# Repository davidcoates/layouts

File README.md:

# keyboards

Everything related to my keyboards.

## Keymaps

QMK "external userspace" layout: keymap sources live under
`keyboards/<keyboard>/keymaps/davidcoates`. Requires Docker.

```
./build nyquist   # compile only, output in bin/
./flash nyquist   # compile (if needed) and flash
```

shannon is defined in this repo (rather than in qmk_firmware) and needs one
firmware per hand -- see `keyboards/shannon/readme.md`:

```
./build shannon-left
./flash shannon-right
```

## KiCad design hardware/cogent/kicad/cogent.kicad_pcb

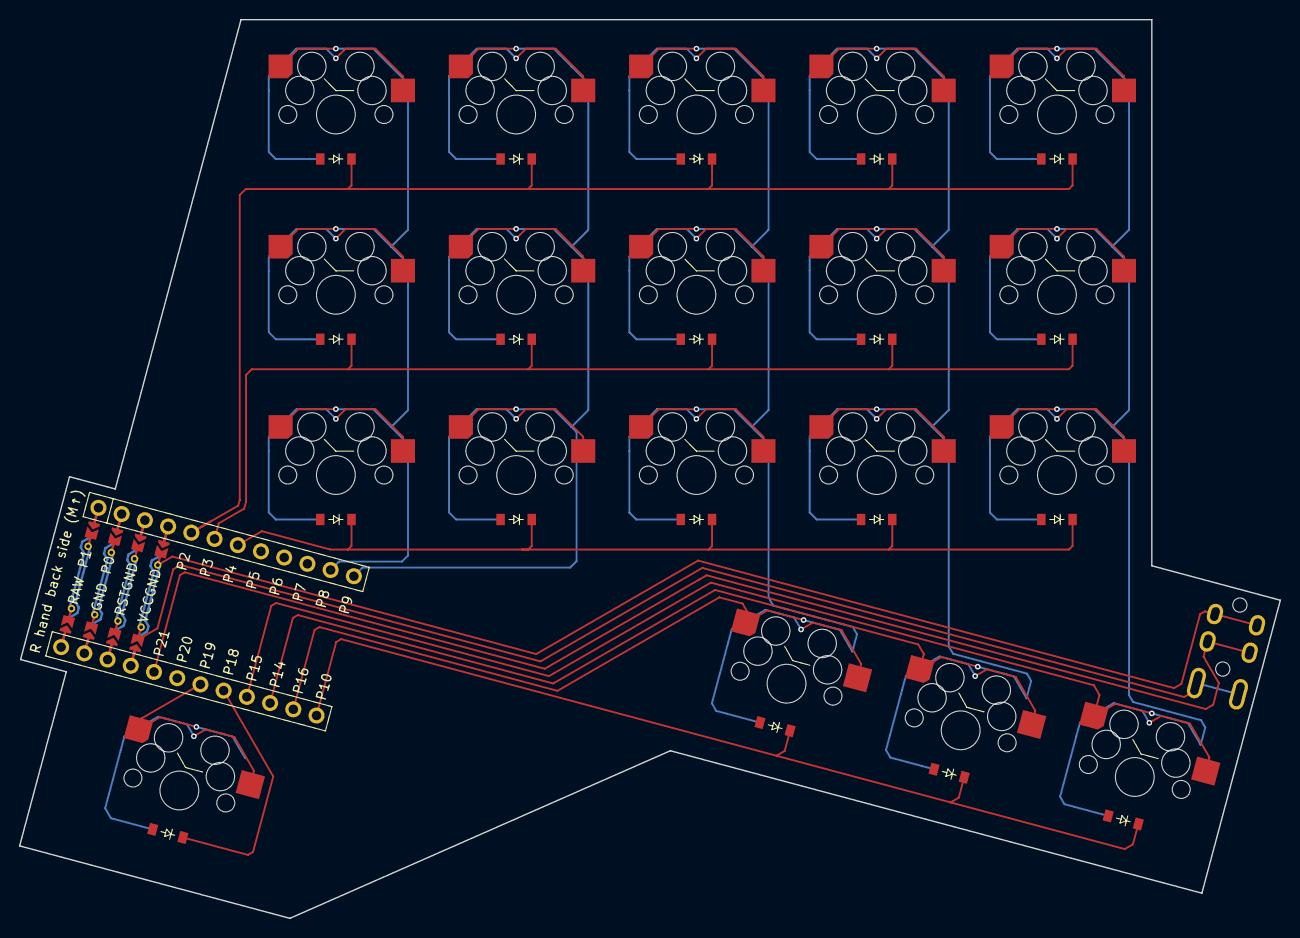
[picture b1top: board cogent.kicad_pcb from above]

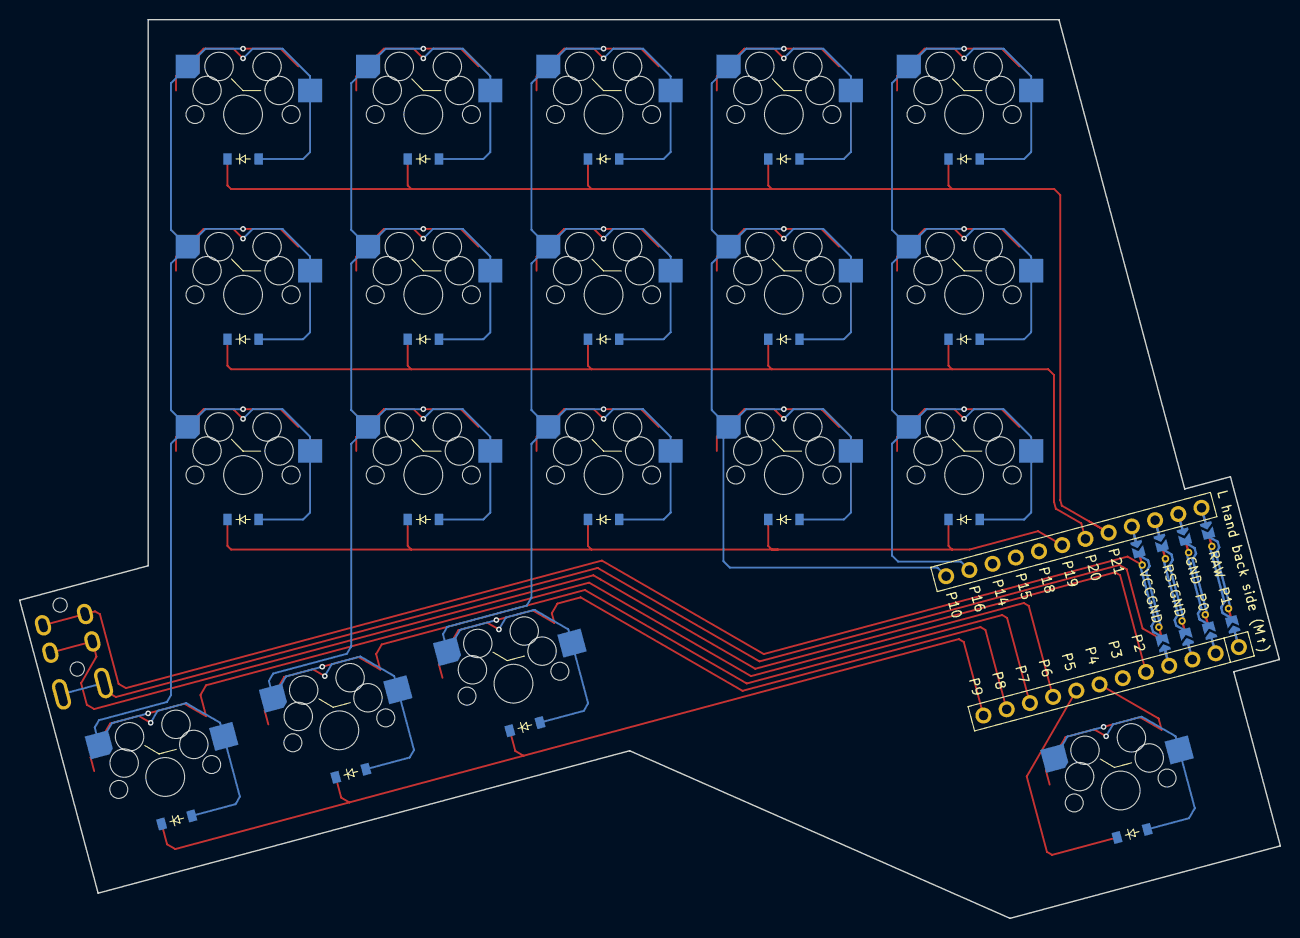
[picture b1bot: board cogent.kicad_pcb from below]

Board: 2 copper layers, 133.2 x 95.0 mm, 40 parts (19 on the bottom side), 33 nets.

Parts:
D1, D2, D3, D4, D5, D6, D7, D8, D9, D10, D11, D12, D13, D14, D15, D16, D17, D18, D19: diode_tht_sod123
MCU1: mcu_nice_nano
S1, S2, S3, S4, S5, S6, S7, S8, S9, S10, S11, S12, S13, S14, S15, S16, S17, S18, S19: switch_mx
TRRS1: trrs_pj320a (reversible, symmetric)

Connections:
GND: MCU1.103, MCU1.104, MCU1.123, TRRS1.2
P2: D3.1, D6.1, D9.1, D12.1, D15.1, MCU1.5
P3: D2.1, D5.1, D8.1, D11.1, D14.1, MCU1.6
P4: D1.1, D4.1, D7.1, D10.1, D13.1, MCU1.7
P8: MCU1.11, S1.2, S2.2, S3.2
P9: MCU1.12, S4.2, S5.2, S6.2
P10: D16.1, D17.1, D18.1, MCU1.13
P14: MCU1.15, S10.2, S11.2, S12.2, S17.2
P15: MCU1.16, S13.2, S14.2, S15.2, S18.2
P16: MCU1.14, S7.2, S8.2, S9.2, S16.2
P18: D19.1, MCU1.17
P19: MCU1.18, S19.2
P21: MCU1.20, TRRS1.3
VCC: MCU1.121, TRRS1.4
center_default: D17.2, S17.1
default_default: D19.2, S19.1
index_bottom: D10.2, S10.1
index_home: D11.2, S11.1
index_top: D12.2, S12.1
inner_bottom: D13.2, S13.1
inner_default: D18.2, S18.1
inner_home: D14.2, S14.1
inner_top: D15.2, S15.1
middle_bottom: D7.2, S7.1
middle_home: D8.2, S8.1
middle_top: D9.2, S9.1
outer_default: D16.2, S16.1
pinky_bottom: D1.2, S1.1
pinky_home: D2.2, S2.1
pinky_top: D3.2, S3.1
ring_bottom: D4.2, S4.1
ring_home: D5.2, S5.1
ring_top: D6.2, S6.1

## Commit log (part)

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2024-09-10 add nyquist
2024-09-10 Create LICENSE
